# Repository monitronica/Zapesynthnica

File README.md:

# ZapeSYNTHnica

> A light-playable, wearable stepped-tone synthesizer for curious hands and ears.

**A project by monitronica**

*A finished ZapeSYNTHnica worn as a bracelet. Photo: Klemen Šali and monitronica, from the [konS ZapeSYNTHnica labbook](https://wiki.alphawave.si/doku.php?id=kons:monika), licensed [CC BY 4.0](https://creativecommons.org/licenses/by/4.0/).*

## Project overview

ZapeSYNTHnica is a small analog synthesizer built directly onto a bracelet-shaped circuit board. Turn its controls, shade its light sensors, or connect it to other sound equipment: the instrument responds with raw square-wave pulses, stepped pitches, and playful electronic noise.

The project brings together experimental sound, DIY electronics, wearable technology, and PCB art. It can be approached as an expressive instrument, an introduction to soldering and analog synthesis, or a compact sound source for further experimentation.

## Concept and background

At the heart of ZapeSYNTHnica is the classic **stepped-tone generator**. Forrest M. Mims III first published the circuit as a “Sound Synthesizer” in *Engineer's Notebook: Integrated Circuit Applications* (1980), and later as a “Stepped Tone Generator.” The electronic-music community came to know versions of it as the **Atari Punk Console**, a name coined by Kaustic Machines in reference to its game-like tones.

ZapeSYNTHnica keeps that deliberately simple analog idea and gives it a wearable, tactile form. Its circuit board is not just a support for components: it is also the body, control surface, and visual identity of the instrument. The design grew through hands-on workshop practice, where making, listening, troubleshooting, and improvising happen together.

The workshop was developed by **monitronica and Klemen Šali** within *Spajkalčki*, a community of creative gatherings for exploring contemporary technologies and practical educational formats. The konS labbook presents the project as a beginner-friendly activity for ages 9 and up. A special limited board version was later designed for a 2023 workshop at Radiona in Zagreb.

## How ZapeSYNTHnica works

The **NE556** contains two 555-style timers in one 14-pin package. In this circuit:

1. The first timer runs as an astable audio oscillator.
2. Its repeating signal triggers the second timer, configured as a monostable multivibrator.
3. The second timer produces square output pulses whose duration is controlled independently.
4. Changing the oscillator rate and pulse duration creates the characteristic stepped-tone response.

Each timing control can use either a potentiometer or a light-dependent resistor (LDR), selected with a switch. Covering an LDR with a hand, moving under a lamp, or casting a moving shadow changes its resistance and therefore the sound. This turns ambient light and gesture into part of the instrument.

## Features and sound interaction

- Two hands-on sound controls for oscillator rate and output-pulse duration
- Two LDRs for playing the circuit with light and shadow
- Switchable manual or light-sensitive control for each timing section
- On-board piezo buzzer for immediate, self-contained sound
- LED activity indicator
- 3.5 mm connections for two external control inputs and one audio output
- CR2025 coin-cell power and an on/off switch
- Bracelet slots for attaching a wrist strap
- A circuit that invites component substitutions and sonic modification

The two external inputs connect to the NE556 control-voltage pins. They make it possible to experiment with external control signals and to place ZapeSYNTHnica alongside modular equipment. Treat it as an experimental interface rather than a standards-compliant Eurorack module: check voltage ranges, grounding, and output level before connecting it to other gear.

## Hardware and electronics

The repository preserves the original technical resources:

- [KiCad schematic](zapeSYNTHnica.sch) — legacy KiCad 5 Eeschema format
- [KiCad PCB design](zapeSYNTHnica4Radiona.kicad_pcb) — the Radiona board layout and PCB artwork
- [Bill of materials](Copy%20of%20zapeSYNTHnicavelenje.xlsx) — workshop quantities and component references
- [Illustrated build instructions](https://wiki.alphawave.si/doku.php?id=kons:monika) — the full konS labbook in Slovenian

The design uses through-hole parts, including an NE556N in a DIP-14 socket, two 1 kΩ resistors, two 100 kΩ potentiometers, two LDRs, two 0.22 µF timing capacitors, one 10 µF polarized capacitor, switches, an LED, a piezo buzzer, three 3.5 mm jacks, and a CR2025 holder. Consult the schematic and the board markings while building; the legacy BOM contains a few inconsistent text labels and is retained unchanged as source documentation.

The example PCB was created in **KiCad 5** with the [Svg2Shenzhen](https://github.com/badgeek/svg2shenzhen) Inkscape extension, which allowed illustration and copper-board design to meet in the same object.

## Photos and documentation

| Finished instrument | Circuit and construction |
| --- | --- |
|  | The [konS labbook](https://wiki.alphawave.si/doku.php?id=kons:monika) contains the schematic, component placement, step-by-step soldering photographs, polarity guidance, and troubleshooting notes. |
| Bracelet with populated PCB and controls. Photo: Klemen Šali and monitronica, CC BY 4.0. | Additional workshop photographs: [Radiona, Zagreb (2023)](https://radiona.org/monika-pocrnjic-radionica-zapesynthnica/) and [Drugo More, Rijeka (2024)](https://www.flickr.com/photos/drugomore/sets/72177720318059783). These remain externally linked because reuse permission is not stated clearly. |

Image provenance and reuse details are recorded in [images/README.md](images/README.md).

## Building your own ZapeSYNTHnica

Start with the [illustrated labbook](https://wiki.alphawave.si/doku.php?id=kons:monika) and use the files in this repository as the technical reference.

1. Review the schematic, PCB layout, and BOM before ordering parts.
2. Gather a temperature-controlled soldering iron, solder, flush cutters, pliers, tape, scissors, and the listed through-hole components.
3. Solder the low-profile parts first: resistors and timing capacitors.
4. Add the DIP socket and switches, observing the socket notch and board outlines.
5. Install the potentiometers, LDRs, battery holder, LED, polarized capacitor, buzzer, and audio jacks. Observe every polarity marking.
6. Insert the NE556 only after soldering is complete, then fit the CR2025 with its positive side facing as marked.
7. Inspect every joint and check for bridges before switching on. If the circuit is silent, remove the battery first, then check orientation, continuity, and solder joints.
8. Attach a suitable strap through the board slots and begin with the controls near their middle positions.

Solder in a ventilated workspace, keep hot tools away from flammable material, and use eye protection when trimming leads. Beginners should build with an experienced facilitator. The source files are fabrication resources, not a tested commercial kit release; verify footprints, clearances, component availability, and fabrication outputs before ordering boards.

## Workshops and educational context

ZapeSYNTHnica is designed for learning by making. A workshop can introduce:

- safe soldering and component orientation
- resistance, capacitance, oscillation, and pulse timing
- the 555/556 timer as a building block for sound
- photoresistors and environmental interaction
- signal flow, audio connections, and control voltage
- troubleshooting through inspection and continuity testing
- the artistic possibilities of circuits worn on the body

The project has appeared in konS educational programming in Maribor, including the **SYNTHbracelet** workshop in December 2021; at **Radiona** in Zagreb in June 2023; and at the **3N / AND Fair** in Rijeka in April 2024. These events frame the instrument as both a first electronics build and an open-ended tool for creative sound practice.

## Credits and acknowledgements

- **Project and artistic direction:** monitronica
- **Workshop concept, development, and labbook:** Klemen Šali and monitronica
- **PCB design:** monitronica; the board silkscreen also acknowledges inspiration from MONO Scarves
- **Workshop production and publication:** MKC Maribor and konS – Platform for Contemporary Investigative Art
- **Original stepped-tone circuit:** Forrest M. Mims III
- **“Atari Punk Console” name:** Kaustic Machines
- **Radiona edition and 2023 workshop host:** Radiona – Zagreb Makerspace
- **2024 workshop documentation:** Drugo More; photographs by Tanja Kanazir / Drugo More

The 2023 konS labbook states that its text and photographs are available under the [Creative Commons Attribution 4.0 International license](https://creativecommons.org/licenses/by/4.0/). The hardware files in this repository do not currently include an explicit hardware license; contact the project author before assuming permission for commercial reuse or redistribution.

## Useful links and resources

- [ZapeSYNTHnica konS labbook and build guide](https://wiki.alphawave.si/doku.php?id=kons:monika)
- [SYNTHbracelet workshop page, konS](https://kons-platforma.org/en/dogodki/synthbracelet/)
- [ZapeSYNTHnica workshop at Radiona, Zagreb](https://radiona.org/monika-pocrnjic-radionica-zapesynthnica/)
- [ZapeSYNTHnica workshop at 3N / AND Fair, Rijeka](https://www.flickr.com/photos/drugomore/sets/72177720318059783)
- [Forrest Mims on the Atari Punk Console circuit](https://www.jameco.com/Jameco/workshop/DIY/atari-punk-console.html)
- [NE556 dual timer datasheet, Texas Instruments](https://www.ti.com/lit/ds/symlink/ne556.pdf)
- [Svg2Shenzhen](https://github.com/badgeek/svg2shenzhen)
- [monitronica on GitHub](https://github.com/monitronica)

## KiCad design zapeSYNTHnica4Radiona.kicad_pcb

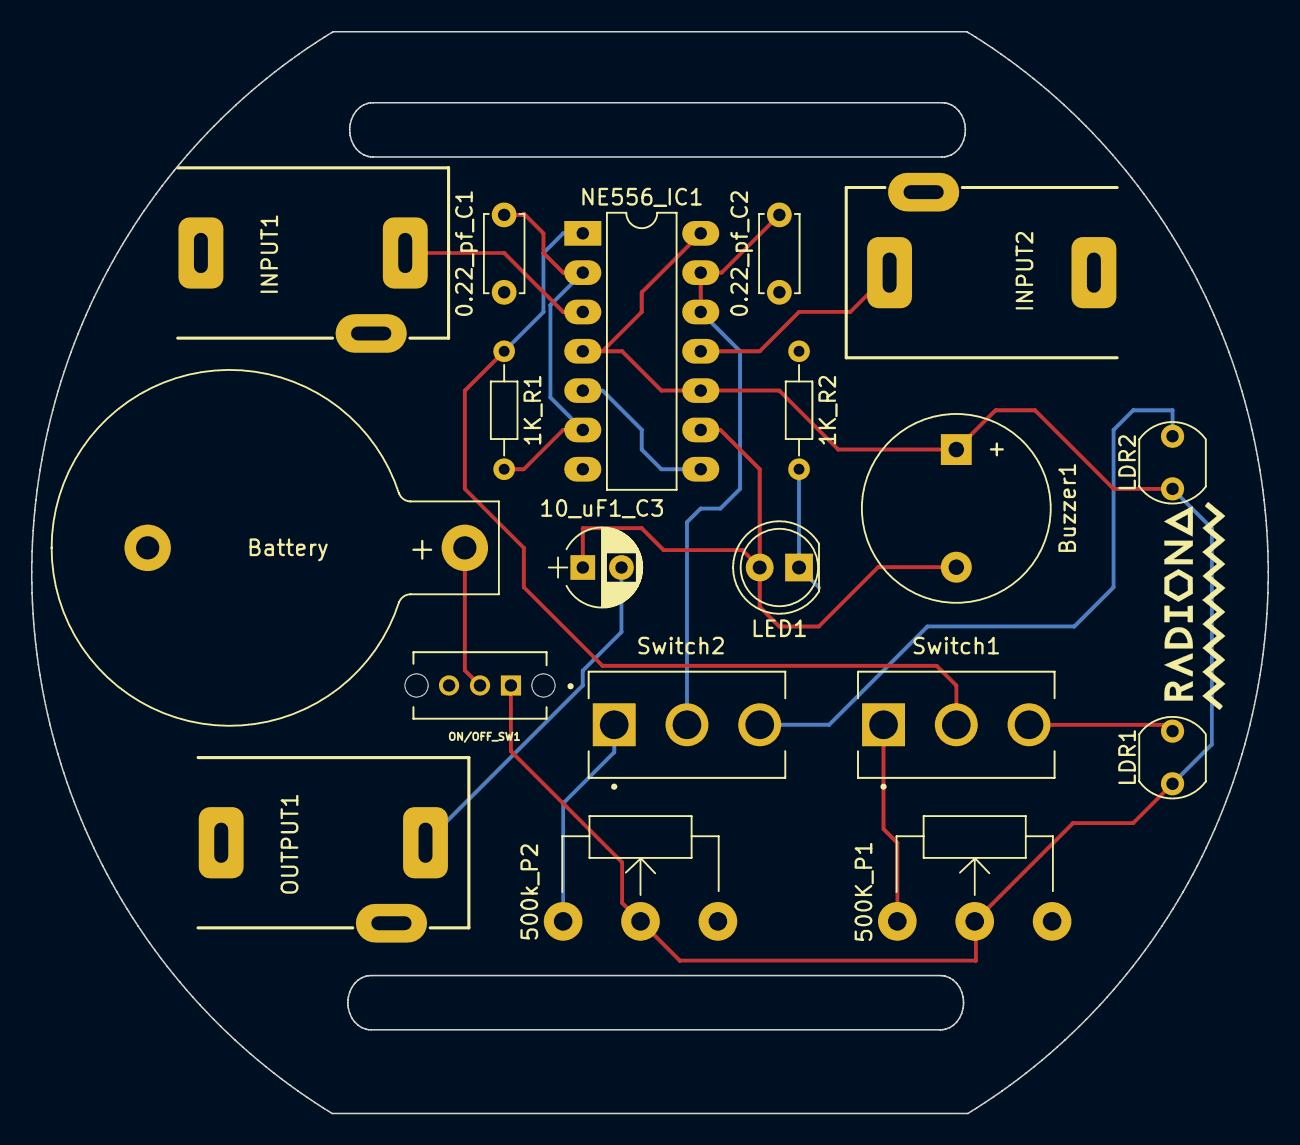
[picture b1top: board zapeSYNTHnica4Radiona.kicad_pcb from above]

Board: 2 copper layers, 79.9 x 69.9 mm, 21 parts (1 on the bottom side), 16 nets.

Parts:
0.22_pf_C1, 0.22_pf_C2: 0.22 pf; C_Disc_D5.0mm_W2.5mm_P5.00mm
1K_R1, 1K_R2: 1 K; R_Axial_DIN0204_L3.6mm_D1.6mm_P7.62mm_Horizontal
10_uF1_C3: CP ! 10 uF; CP_Radial_D5.0mm_P2.50mm
500K_P1, 500k_P2: 500K; Potentiometer_WirePads
Battery: Battery_Cell; BatteryHolder_Keystone_103_1x20mm
Buzzer1: Buzzer; Buzzer_12x9.5RM7.6
INPUT1, INPUT2: AudioJack3; Jack_3.5mm_QingPu_WQP-PJ302M_Horizontal
LDR1: 1; Resistor_LDR_5.1x4.3_RM3.4
LDR2: 2; Resistor_LDR_5.1x4.3_RM3.4
LED1: LED; LED_D5.0mm
NE556_IC1: NE556N; DIP-14_W7.62mm_LongPads
ON/OFF_SW1: SW_SPDT; SW_OS102011MS2QN1
OUTPUT1: AudioJack3; Jack_3.5mm_QingPu_WQP-PJ302M_Horizontal
Ref**: Val**; radionedisn
Ref**#2: Val**; radionedisn
Switch1, Switch2: SW_SPDT; SW_100SP1T1B4M2QE

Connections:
GND: 0.22_pf_C1.1, 0.22_pf_C2.1, 1K_R2.1, Battery.2, INPUT1.S, INPUT2.S, NE556_IC1.7, OUTPUT1.S
unnamed: 0.22_pf_C1.2, 1K_R1.2, NE556_IC1.2, NE556_IC1.6
unnamed: 0.22_pf_C2.2, NE556_IC1.12, NE556_IC1.13, Switch2.2
unnamed: 1K_R2.2, LED1.1
unnamed: 1K_R1.1, NE556_IC1.1, Switch1.2
unnamed: 10_uF1_C3.1, Buzzer1.2, LED1.2, NE556_IC1.9
unnamed: 10_uF1_C3.2, OUTPUT1.T
unnamed: 500K_P1.1, Switch1.1
unnamed: 500k_P2.1, Switch2.1
unnamed: Battery.1, ON/OFF_SW1.2
unnamed: INPUT1.T, NE556_IC1.3
unnamed: INPUT2.T, NE556_IC1.11
unnamed: LDR1.2, Switch1.3
unnamed: LDR2.2, Switch2.3
unnamed: NE556_IC1.5, NE556_IC1.8
VCC: 500K_P1.2, 500k_P2.2, Buzzer1.1, LDR1.1, LDR2.1, NE556_IC1.4, NE556_IC1.10, NE556_IC1.14, ON/OFF_SW1.1
